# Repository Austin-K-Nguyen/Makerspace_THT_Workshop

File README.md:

<p align="center">
  <image src="https://github.com/Austin-K-Nguyen/Makerspace_THT_Workshop/blob/main/Images/makerspace_logo.png">
</p>
<h1 align="center">Makerspace THT Workshop Dino</h1>

<h2 align="left">About</h2>

Introducing! The newest soldering workshop developed for the Schulich School of Engineering Makermultipliex and Zetta, the new Voltage Sniffing Rex!

Created as a cool educational toy and NOT as a replacement or alternative to a REAL electrical tester, the Voltage Sniffing Rex can detect and react to live wires containing AC voltages.

This prototype aims to introduce beginners to basic through-hole soldering techniques and safety in a new and interactive way. The contents of this repo should provide 
all the files necessary to produce these dinos for yourself.

For more information about equipment, trainings and classes offered within the Makermultiplex visit https://schulich.libguides.com/m2z/.
And for more cool dino themed project kits, checkout the Flex-E Rex Soldering Kit here https://github.com/Lee-F-Evans/Flex-E-Rex-Soldering-Kit

<h2 align="left">Gathering Parts</h2>

To create the kits you'll need to order some PCBS, gather all the nessassary parts listed in the BOM excel sheet, and grab some basic soldering tools.

<h2 align="left">PCB Fabrication</h2>

The repo above should include both KiCad project files should you feel like viewing or modifying them, and also ready made gerbers and image reference files (TBA) that can be used directly for PCB manufacturing.

The PCB's were order from PCBWay as they provide full UV colour printing onto PCB's using simple image files and some extra silkscren work when designing the PCB. 

* Of note as of writing this, other manufacturers such as JLC PCB do also provide full colour printing, but require you to use their own deisgn software for it to work, as such unless this changes I reccomended using PCBWay as your main board manufacturer.

<h2 align="left">Parts</h2>

The provided bill of materials or BOM provided above, details all the nessassary parts required for this kit. The BOM along with listing parts, also links Digi-Key part listings should you wish to order them from them, though ordering the parts from any vendor should also work.
<h4 align="left">Part Substitutions</h4>

* A note on the 555 timer ic, the LMC555 timer spcificed in the BOM does have a standard pinout so feel free to change the chip out for any numerious different versions of the 555 chip, though it MUST be able to operate at atleast 3V preferably below and share the same standard pinout.

* A note on the LM358 op-amp ic, again this 8-pin duel op-amp ic has a standard pinout, so feel free to change out the chip for any number of duel op-amp, 8-pin, standard pinout ics that operate at preferably below 3v.

<h2 align="left">Tools</h2>

You'll only need the basic tools to solder for this this kit including,
* Soldering Iron
* Lead-Free Solder
* Flush Cutters / Wire Cutters

And Thats it!

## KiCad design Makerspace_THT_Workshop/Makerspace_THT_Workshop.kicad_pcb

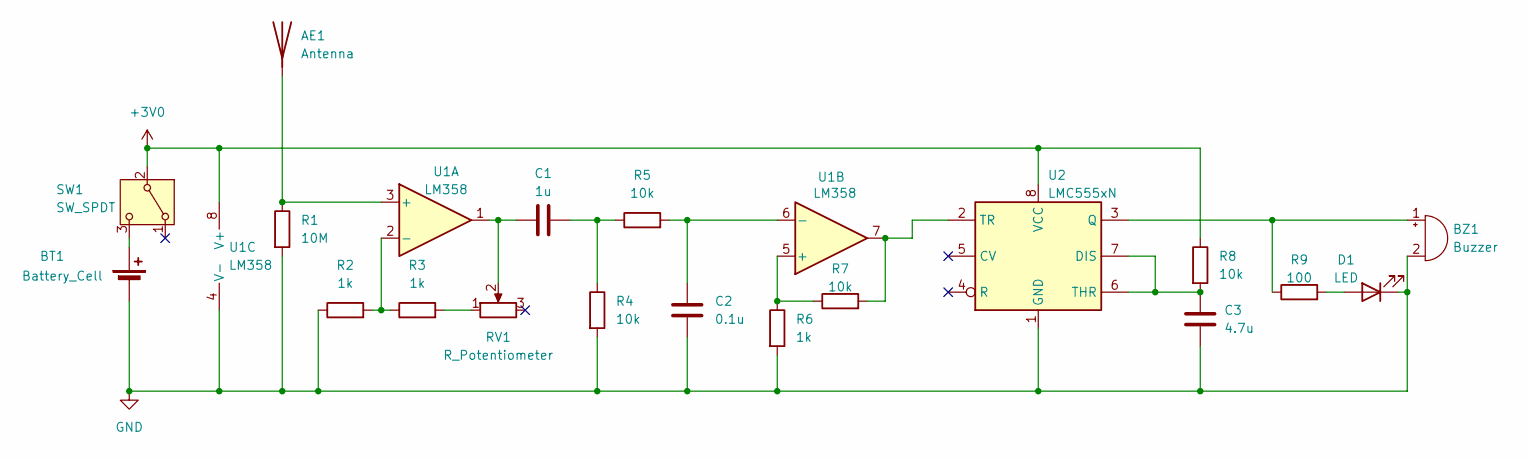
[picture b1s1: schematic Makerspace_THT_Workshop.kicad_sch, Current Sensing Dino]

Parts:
AE1: Antenna; TestPoint_Pad_D4.0mm
BT1: Battery_Cell; BK-913_MPD
BZ1: Buzzer; Buzzer_TDK_PS1240P02BT_D12.2mm_H6.5mm
C1: 1u; C_Disc_D5.1mm_W3.2mm_P5.00mm
C2: 0.1u; C_Disc_D4.3mm_W1.9mm_P5.00mm
C3: 4.7u; C_Disc_D4.3mm_W1.9mm_P5.00mm
D1: LED; LED_D5.0mm_5.0mm_Pitch
R1: 10M; R_Axial_DIN0207_L6.3mm_D2.5mm_P10.16mm_Horizontal
R2, R3, R6: 1k; R_Axial_DIN0207_L6.3mm_D2.5mm_P10.16mm_Horizontal
R4, R5, R7, R8: 10k; R_Axial_DIN0207_L6.3mm_D2.5mm_P10.16mm_Horizontal
R9: 100; R_Axial_DIN0207_L6.3mm_D2.5mm_P10.16mm_Horizontal
RV1: R_Potentiometer; 601030_AVX
SW1: SW_SPDT; SW_Slide_SPDT_Angled_CK_OS102011MA1Q
U1: LM358; DIP-8_W7.62mm_Socket_LongPads
U2: LMC555xN; DIP-8_W7.62mm_Socket_LongPads

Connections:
+3V0: R8.1, SW1.2 (B), U1.8 (V+), U2.8 (VCC)
GND: BT1.2 (-), BZ1.2 (-), C2.1, C3.2, D1.1 (K), R1.2, R2.1, R4.2, R6.2, U1.4 (V-), U2.1 (GND)
unnamed: AE1.1 (A), R1.1, U1.3 (+)
unnamed: BT1.1 (+), SW1.3 (C)
unnamed: BZ1.1 (+), R9.1, U2.3 (Q)
unnamed: C1.1, RV1.2, U1.1
unnamed: C1.2, R4.1, R5.1
unnamed: D1.2 (A), R9.2
unnamed: R3.2, RV1.1
unnamed: R2.2, R3.1, U1.2 (-)
unnamed: R6.1, R7.1, U1.5 (+)
unnamed: C2.2, R5.2, U1.6 (-)
unnamed: C3.1, R8.2, U2.6 (THR), U2.7 (DIS)
unnamed: R7.2, U1.7, U2.2 (TR)

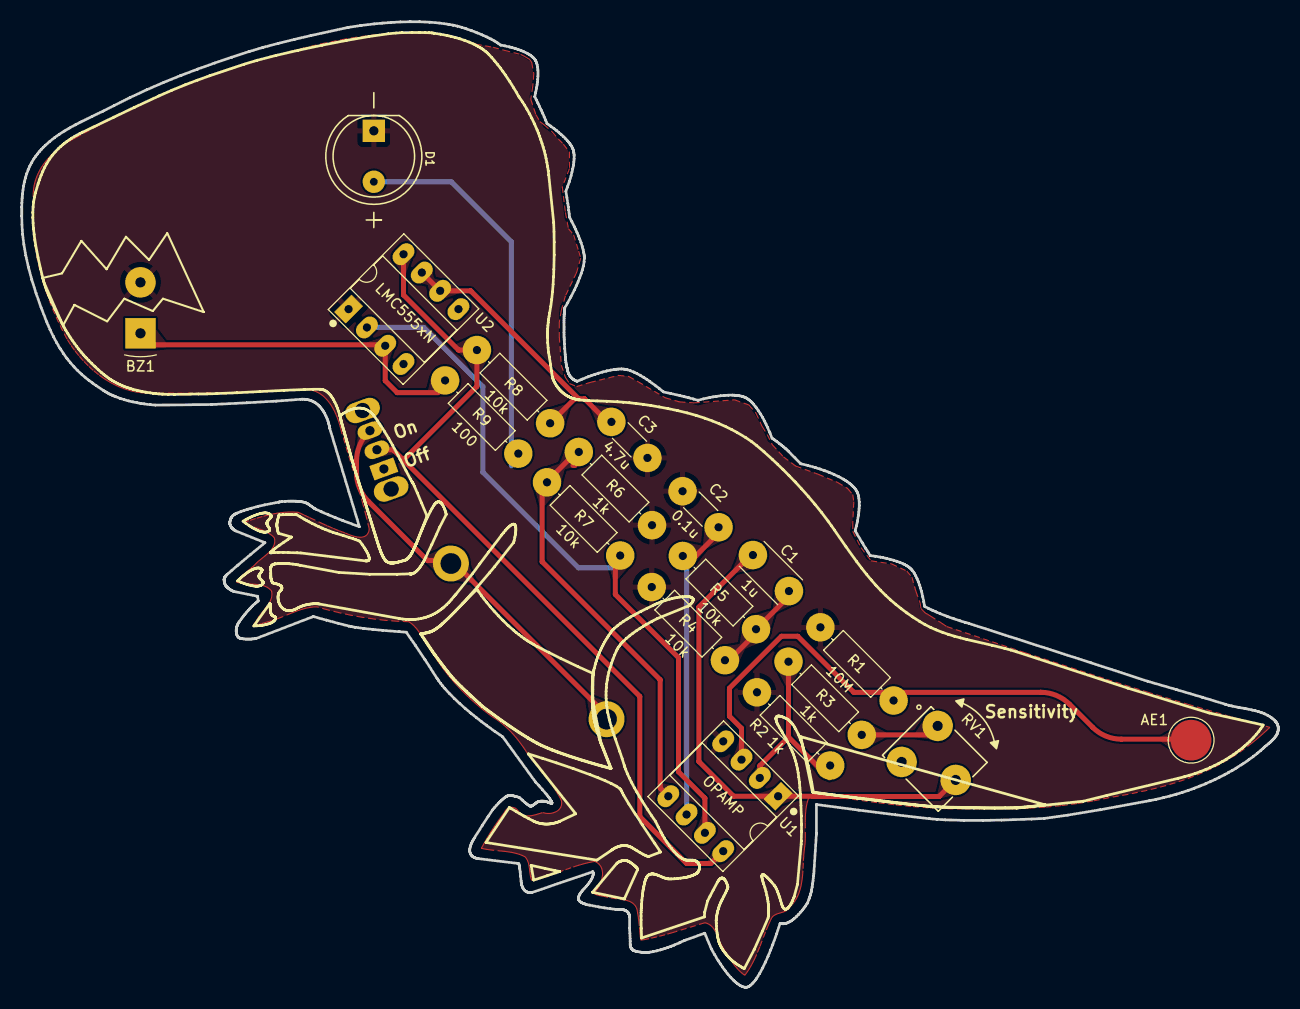
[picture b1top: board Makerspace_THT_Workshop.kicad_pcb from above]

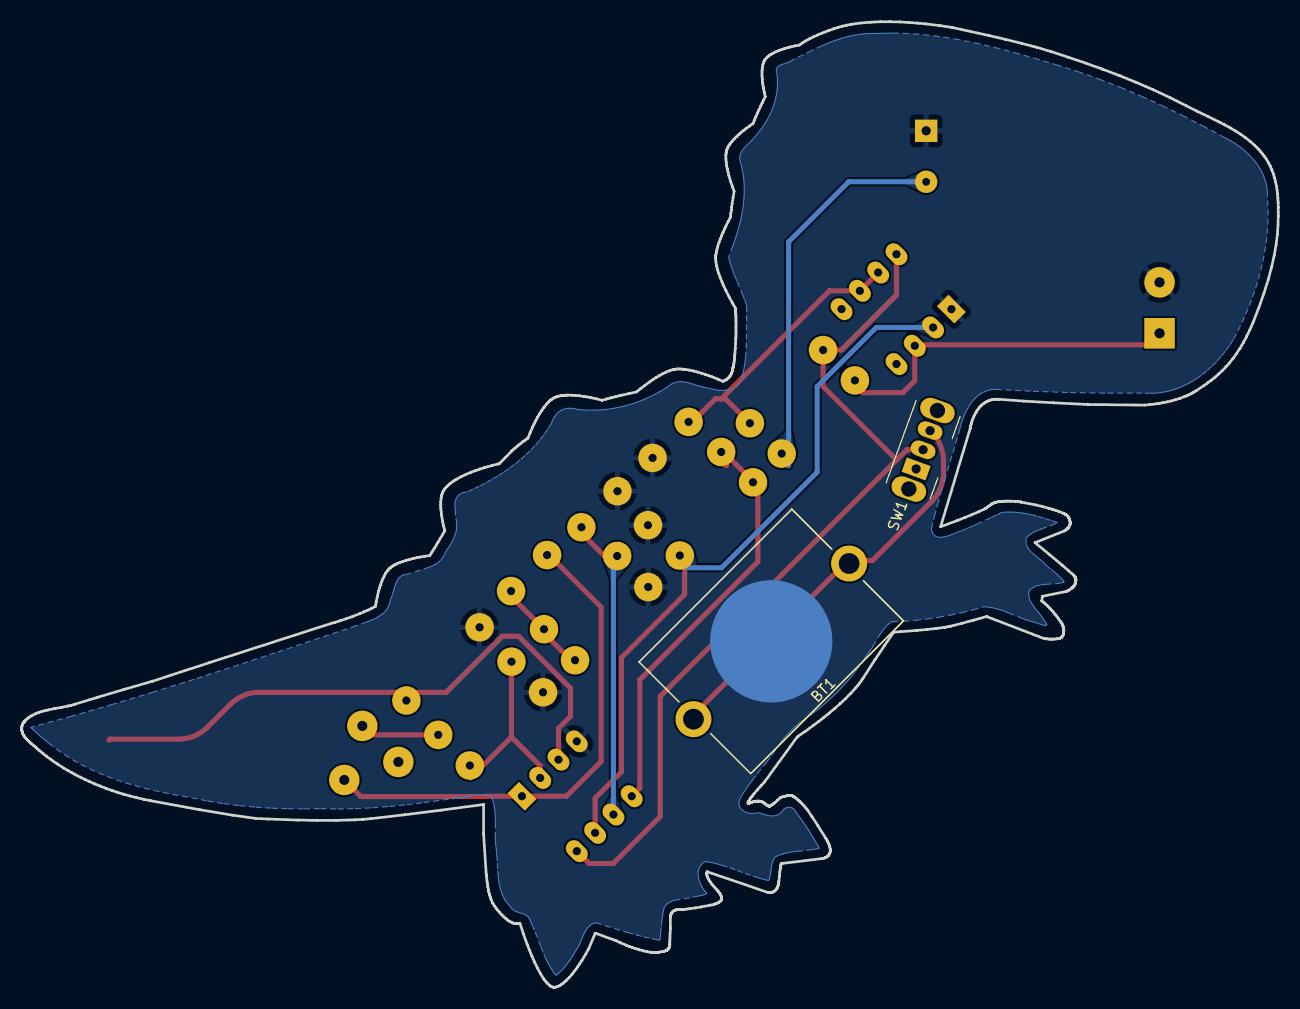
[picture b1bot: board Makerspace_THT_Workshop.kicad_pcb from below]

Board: 2 copper layers, 123.3 x 94.8 mm, 20 parts (2 on the bottom side), 14 nets.

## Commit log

2024-12-09 Intial commit, includes all initial pcb and schem diagrams
2024-12-09 Just adding some assets
2024-12-10 Updated PCB with testpoints and text
2024-12-12 Added some more detail to pcb and more assets
2024-12-13 Added gerb files
2025-02-19 Updated the board to fix alot of stuff
2025-03-07 New Version of the PCB layout
2025-03-18 Minor Layout Changes
2025-09-12 Updated PCB layout, vectors, and updated references
